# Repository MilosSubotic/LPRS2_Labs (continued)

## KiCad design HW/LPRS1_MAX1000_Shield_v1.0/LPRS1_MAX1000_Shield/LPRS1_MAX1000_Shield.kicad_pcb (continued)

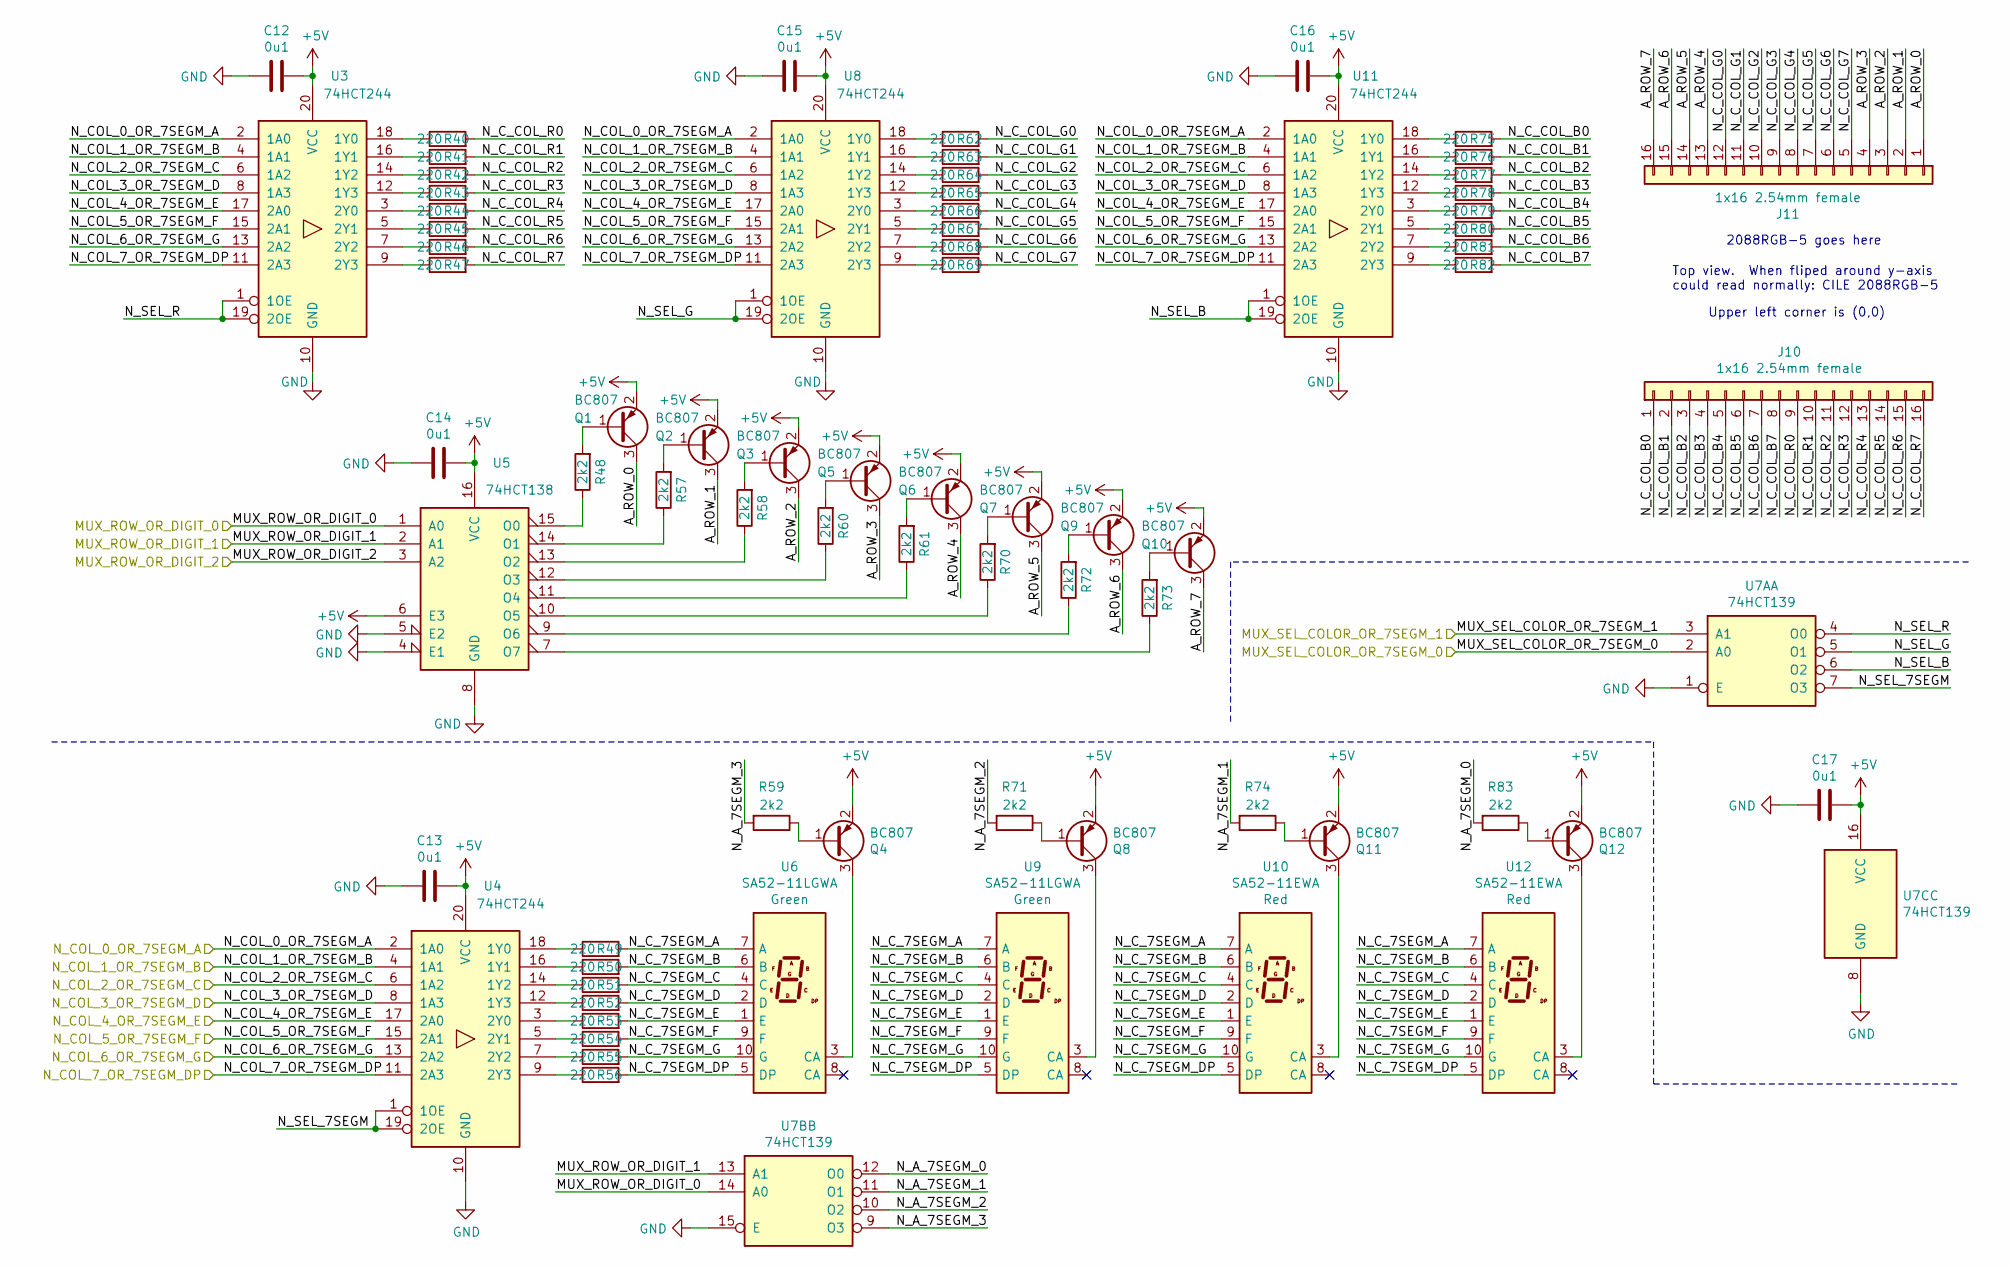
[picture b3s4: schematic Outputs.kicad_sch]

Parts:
C12, C13, C14, C15, C16, C17: 0u1; C_0805_2012Metric_Pad1.15x1.40mm_HandSolder
J10, J11: 1x16 2.54mm female; PinSocket_1x16_P2.54mm_Vertical
Q1, Q2, Q3, Q4, Q5, Q6, Q7, Q8, Q9, Q10, Q11, Q12: BC807; SOT-23
R40, R41, R42, R43, R44, R45, R46, R47, R49, R50, R51, R52, R53, R54, R55, R56, R62, R63, R64, R65, R66, R67, R68, R69, R75, R76, R77, R78, R79, R80, R81, R82: 220; R_0805_2012Metric_Pad1.15x1.40mm_HandSolder
R48, R57, R58, R59, R60, R61, R70, R71, R72, R73, R74, R83: 2k2; R_0805_2012Metric_Pad1.15x1.40mm_HandSolder
U3, U4, U8, U11: 74HCT244; SOIC-20W_7.5x12.8mm_P1.27mm
U5: 74HCT138; SOIC-16_3.9x9.9mm_P1.27mm
U6, U9: SA52-11LGWA; 7SegmentLED_LTS6760_LTS6780
U7A, U7B, U7C: 74HCT139; SOIC-16_3.9x9.9mm_P1.27mm
U10, U12: SA52-11EWA; 7SegmentLED_LTS6760_LTS6780

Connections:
+5V: C12.1, C13.1, C14.1, C15.1, C16.1, C17.1, Q1.2 (E), Q2.2 (E), Q3.2 (E), Q4.2 (E), Q5.2 (E), Q6.2 (E), Q7.2 (E), Q8.2 (E), Q9.2 (E), Q10.2 (E), Q11.2 (E), Q12.2 (E), U3.20 (VCC), U4.20 (VCC), U5.6 (E3), U5.16 (VCC), U7C.16 (VCC), U8.20 (VCC), U11.20 (VCC); also elsewhere on the board
/Outputs/A_ROW_0: J11.1, Q1.3 (C)
/Outputs/A_ROW_1: J11.2, Q2.3 (C)
/Outputs/A_ROW_2: J11.3, Q3.3 (C)
/Outputs/A_ROW_3: J11.4, Q5.3 (C)
/Outputs/A_ROW_4: J11.13, Q6.3 (C)
/Outputs/A_ROW_5: J11.14, Q7.3 (C)
/Outputs/A_ROW_6: J11.15, Q9.3 (C)
/Outputs/A_ROW_7: J11.16, Q10.3 (C)
/Outputs/MUX_ROW_OR_DIGIT_0: U5.1 (A0), U7B.14 (A0); also elsewhere on the board
/Outputs/MUX_ROW_OR_DIGIT_1: U5.2 (A1), U7B.13 (A1); also elsewhere on the board
/Outputs/MUX_ROW_OR_DIGIT_2: U5.3 (A2); also elsewhere on the board
/Outputs/N_A_7SEGM_0: R83.2, U7B.12 (O0); also elsewhere on the board
/Outputs/N_A_7SEGM_1: R74.2, U7B.11 (O1); also elsewhere on the board
/Outputs/N_A_7SEGM_2: R71.2, U7B.10 (O2); also elsewhere on the board
/Outputs/N_A_7SEGM_3: R59.2, U7B.9 (O3); also elsewhere on the board
/Outputs/N_COL_0_OR_7SEGM_A: U3.2 (1A0), U4.2 (1A0), U8.2 (1A0), U11.2 (1A0); also elsewhere on the board
/Outputs/N_COL_1_OR_7SEGM_B: U3.4 (1A1), U4.4 (1A1), U8.4 (1A1), U11.4 (1A1); also elsewhere on the board
/Outputs/N_COL_2_OR_7SEGM_C: U3.6 (1A2), U4.6 (1A2), U8.6 (1A2), U11.6 (1A2); also elsewhere on the board
/Outputs/N_COL_3_OR_7SEGM_D: U3.8 (1A3), U4.8 (1A3), U8.8 (1A3), U11.8 (1A3); also elsewhere on the board
/Outputs/N_COL_4_OR_7SEGM_E: U3.17 (2A0), U4.17 (2A0), U8.17 (2A0), U11.17 (2A0); also elsewhere on the board
/Outputs/N_COL_5_OR_7SEGM_F: U3.15 (2A1), U4.15 (2A1), U8.15 (2A1), U11.15 (2A1); also elsewhere on the board
/Outputs/N_COL_6_OR_7SEGM_G: U3.13 (2A2), U4.13 (2A2), U8.13 (2A2), U11.13 (2A2); also elsewhere on the board
/Outputs/N_COL_7_OR_7SEGM_DP: U3.11 (2A3), U4.11 (2A3), U8.11 (2A3), U11.11 (2A3); also elsewhere on the board
/Outputs/N_C_7SEGM_A: R49.2, U6.7 (A), U9.7 (A), U10.7 (A), U12.7 (A)
/Outputs/N_C_7SEGM_B: R50.2, U6.6 (B), U9.6 (B), U10.6 (B), U12.6 (B)
/Outputs/N_C_7SEGM_C: R51.2, U6.4 (C), U9.4 (C), U10.4 (C), U12.4 (C)
/Outputs/N_C_7SEGM_D: R52.2, U6.2 (D), U9.2 (D), U10.2 (D), U12.2 (D)
/Outputs/N_C_7SEGM_DP: R56.2, U6.5 (DP), U9.5 (DP), U10.5 (DP), U12.5 (DP)
/Outputs/N_C_7SEGM_E: R53.2, U6.1 (E), U9.1 (E), U10.1 (E), U12.1 (E)
/Outputs/N_C_7SEGM_F: R54.2, U6.9 (F), U9.9 (F), U10.9 (F), U12.9 (F)
/Outputs/N_C_7SEGM_G: R55.2, U6.10 (G), U9.10 (G), U10.10 (G), U12.10 (G)
/Outputs/N_C_COL_B0: J10.1, R75.2
/Outputs/N_C_COL_B1: J10.2, R76.2
/Outputs/N_C_COL_B2: J10.3, R77.2
/Outputs/N_C_COL_B3: J10.4, R78.2
/Outputs/N_C_COL_B4: J10.5, R79.2
/Outputs/N_C_COL_B5: J10.6, R80.2
/Outputs/N_C_COL_B6: J10.7, R81.2
/Outputs/N_C_COL_B7: J10.8, R82.2
/Outputs/N_C_COL_G0: J11.12, R62.2
/Outputs/N_C_COL_G1: J11.11, R63.2
/Outputs/N_C_COL_G2: J11.10, R64.2
/Outputs/N_C_COL_G3: J11.9, R65.2
/Outputs/N_C_COL_G4: J11.8, R66.2
/Outputs/N_C_COL_G5: J11.7, R67.2
/Outputs/N_C_COL_G6: J11.6, R68.2
/Outputs/N_C_COL_G7: J11.5, R69.2
/Outputs/N_C_COL_R0: J10.9, R40.2
/Outputs/N_C_COL_R1: J10.10, R41.2
/Outputs/N_C_COL_R2: J10.11, R42.2
/Outputs/N_C_COL_R3: J10.12, R43.2
/Outputs/N_C_COL_R4: J10.13, R44.2
/Outputs/N_C_COL_R5: J10.14, R45.2
/Outputs/N_C_COL_R6: J10.15, R46.2
/Outputs/N_C_COL_R7: J10.16, R47.2
/Outputs/N_SEL_7SEGM: U4.1 (1OE), U4.19 (2OE), U7A.7 (O3); also elsewhere on the board
/Outputs/N_SEL_B: U7A.6 (O2), U11.1 (1OE), U11.19 (2OE); also elsewhere on the board
/Outputs/N_SEL_G: U7A.5 (O1), U8.1 (1OE), U8.19 (2OE); also elsewhere on the board
/Outputs/N_SEL_R: U3.1 (1OE), U3.19 (2OE), U7A.4 (O0); also elsewhere on the board
GND: C12.2, C13.2, C14.2, C15.2, C16.2, C17.2, U3.10 (GND), U4.10 (GND), U5.4 (E1), U5.5 (E2), U5.8 (GND), U7A.1 (E), U7B.15 (E), U7C.8 (GND), U8.10 (GND), U11.10 (GND); also elsewhere on the board
unnamed: Q1.1 (B), R48.2
unnamed: Q2.1 (B), R57.2
unnamed: Q3.1 (B), R58.2
unnamed: Q4.1 (B), R59.1
unnamed: Q4.3 (C), U6.3 (CA)
unnamed: Q5.1 (B), R60.2
unnamed: Q6.1 (B), R61.2
unnamed: Q7.1 (B), R70.2
unnamed: Q8.1 (B), R71.1
unnamed: Q8.3 (C), U9.3 (CA)
unnamed: Q9.1 (B), R72.2
unnamed: Q10.1 (B), R73.2
unnamed: Q11.1 (B), R74.1
unnamed: Q11.3 (C), U10.3 (CA)
unnamed: Q12.1 (B), R83.1
unnamed: Q12.3 (C), U12.3 (CA)
unnamed: R40.1, U3.18 (1Y0)
unnamed: R41.1, U3.16 (1Y1)
unnamed: R42.1, U3.14 (1Y2)
unnamed: R43.1, U3.12 (1Y3)
unnamed: R44.1, U3.3 (2Y0)
unnamed: R45.1, U3.5 (2Y1)
unnamed: R46.1, U3.7 (2Y2)
unnamed: R47.1, U3.9 (2Y3)
unnamed: R48.1, U5.15 (O0)
unnamed: R49.1, U4.18 (1Y0)
unnamed: R50.1, U4.16 (1Y1)
unnamed: R51.1, U4.14 (1Y2)
unnamed: R52.1, U4.12 (1Y3)
unnamed: R53.1, U4.3 (2Y0)
unnamed: R54.1, U4.5 (2Y1)
unnamed: R55.1, U4.7 (2Y2)
unnamed: R56.1, U4.9 (2Y3)
unnamed: R57.1, U5.14 (O1)
unnamed: R58.1, U5.13 (O2)
unnamed: R60.1, U5.12 (O3)
unnamed: R61.1, U5.11 (O4)
unnamed: R62.1, U8.18 (1Y0)
unnamed: R63.1, U8.16 (1Y1)
unnamed: R64.1, U8.14 (1Y2)
unnamed: R65.1, U8.12 (1Y3)
unnamed: R66.1, U8.3 (2Y0)
unnamed: R67.1, U8.5 (2Y1)
unnamed: R68.1, U8.7 (2Y2)
unnamed: R69.1, U8.9 (2Y3)
unnamed: R70.1, U5.10 (O5)
unnamed: R72.1, U5.9 (O6)
unnamed: R73.1, U5.7 (O7)
unnamed: R75.1, U11.18 (1Y0)
unnamed: R76.1, U11.16 (1Y1)
unnamed: R77.1, U11.14 (1Y2)
unnamed: R78.1, U11.12 (1Y3)
unnamed: R79.1, U11.3 (2Y0)
unnamed: R80.1, U11.5 (2Y1)
unnamed: R81.1, U11.7 (2Y2)
unnamed: R82.1, U11.9 (2Y3)

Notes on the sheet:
2088RGB-5 goes here
Top view. When fliped around y-axis could read normally: CILE 2088RGB-5
Upper left corner is (0,0)

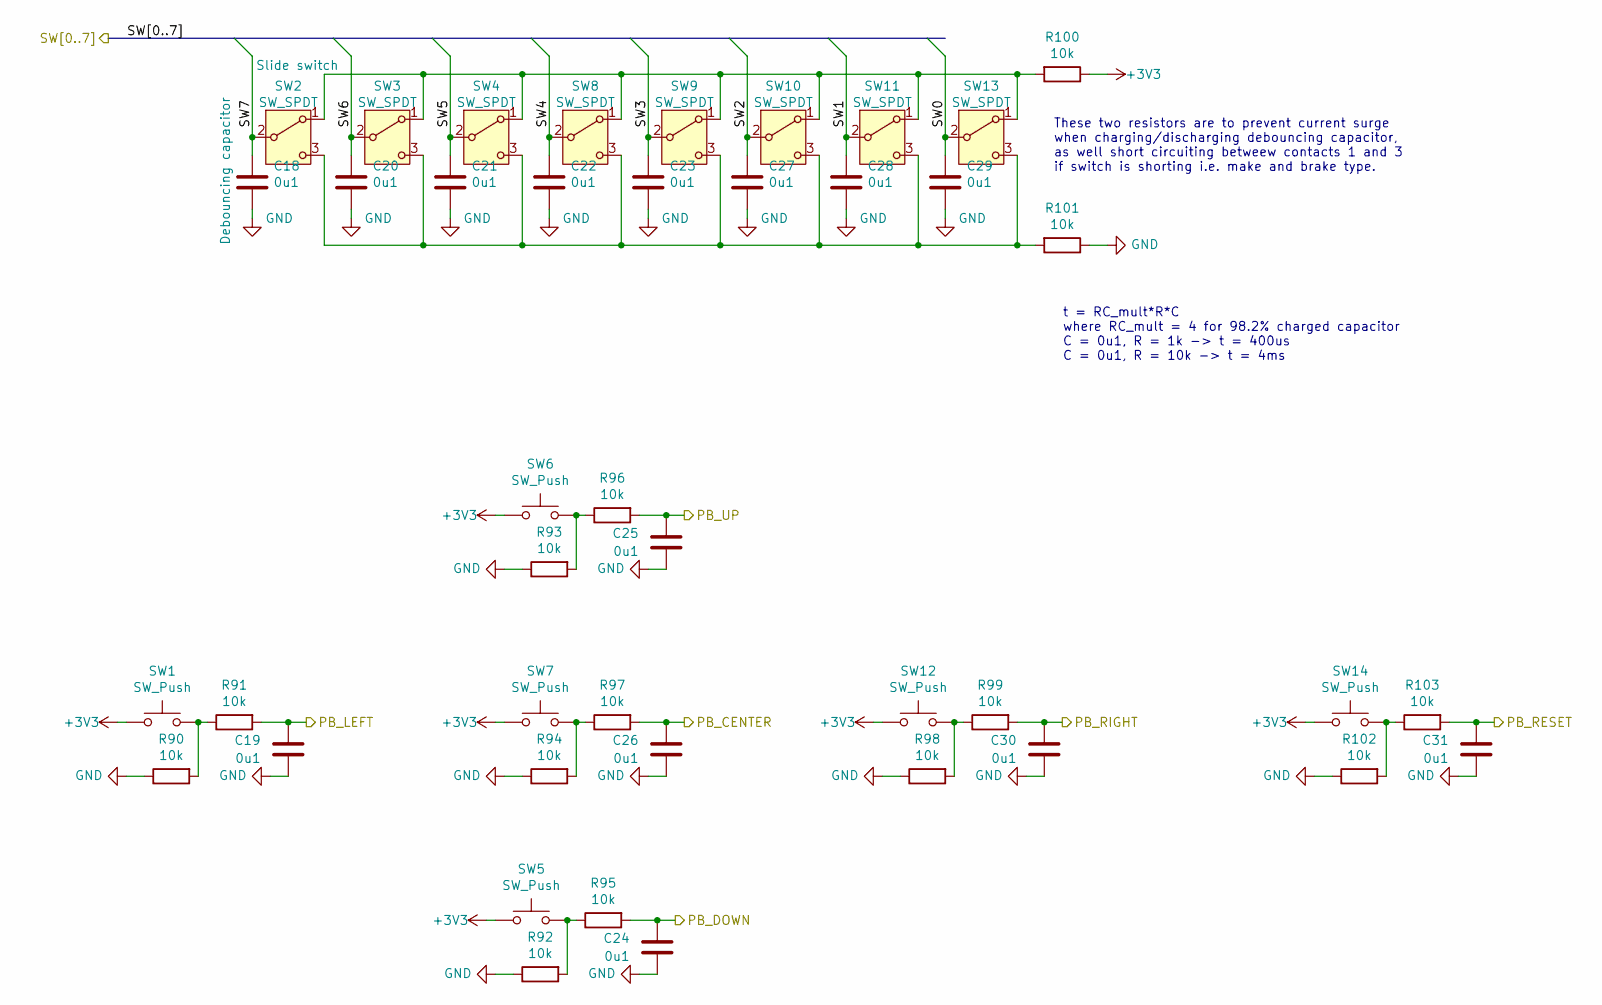
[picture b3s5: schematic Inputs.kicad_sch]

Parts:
C18, C19, C20, C21, C22, C23, C24, C25, C26, C27, C28, C29, C30, C31: 0u1; C_0805_2012Metric_Pad1.15x1.40mm_HandSolder
R90, R91, R92, R93, R94, R95, R96, R97, R98, R99, R100, R101, R102, R103: 10k; R_0805_2012Metric_Pad1.15x1.40mm_HandSolder
SW1, SW5, SW6, SW7, SW12, SW14: SW_Push; SW_PUSH_6mm_H7.3mm
SW2, SW3, SW4, SW8, SW9, SW10, SW11, SW13: SW_SPDT; OS102011MS2QN1

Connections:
+3V3: R100.1, SW1.2, SW5.2, SW6.2, SW7.2, SW12.2, SW14.2; also elsewhere on the board
/Inputs/PB_CENTER: C26.1, R97.2; also elsewhere on the board
/Inputs/PB_DOWN: C24.1, R95.2; also elsewhere on the board
/Inputs/PB_LEFT: C19.1, R91.2; also elsewhere on the board
/Inputs/PB_RESET: C31.1, R103.2; also elsewhere on the board
/Inputs/PB_RIGHT: C30.1, R99.2; also elsewhere on the board
/Inputs/PB_UP: C25.1, R96.2; also elsewhere on the board
/SW0: C29.1, SW13.2 (B); also elsewhere on the board
/SW1: C28.1, SW11.2 (B); also elsewhere on the board
/SW2: C27.1, SW10.2 (B); also elsewhere on the board
/SW3: C23.1, SW9.2 (B); also elsewhere on the board
/SW4: C22.1, SW8.2 (B); also elsewhere on the board
/SW5: C21.1, SW4.2 (B); also elsewhere on the board
/SW6: C20.1, SW3.2 (B); also elsewhere on the board
/SW7: C18.1, SW2.2 (B); also elsewhere on the board
GND: C18.2, C19.2, C20.2, C21.2, C22.2, C23.2, C24.2, C25.2, C26.2, C27.2, C28.2, C29.2, C30.2, C31.2, R90.1, R92.1, R93.1, R94.1, R98.1, R101.1, R102.1, SW2.shield, SW3.shield, SW4.shield, SW8.shield, SW9.shield, SW10.shield, SW11.shield, SW13.shield; also elsewhere on the board
unnamed: R90.2, R91.1, SW1.1
unnamed: R92.2, R95.1, SW5.1
unnamed: R93.2, R96.1, SW6.1
unnamed: R94.2, R97.1, SW7.1
unnamed: R98.2, R99.1, SW12.1
unnamed: R100.2, SW2.1 (A), SW3.1 (A), SW4.1 (A), SW8.1 (A), SW9.1 (A), SW10.1 (A), SW11.1 (A), SW13.1 (A)
unnamed: R101.2, SW2.3 (C), SW3.3 (C), SW4.3 (C), SW8.3 (C), SW9.3 (C), SW10.3 (C), SW11.3 (C), SW13.3 (C)
unnamed: R102.2, R103.1, SW14.1

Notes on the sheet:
t = RC_mult*R*C where RC_mult = 4 for 98.2% charged capacitor C = 0u1, R = 1k -> t = 400us C = 0u1, R = 10k -> t = 4ms
These two resistors are to prevent current surge when charging/discharging debouncing capacitor, as well short circuiting betweew contacts 1 and 3 if switch is shorting i.e. make and brake type.

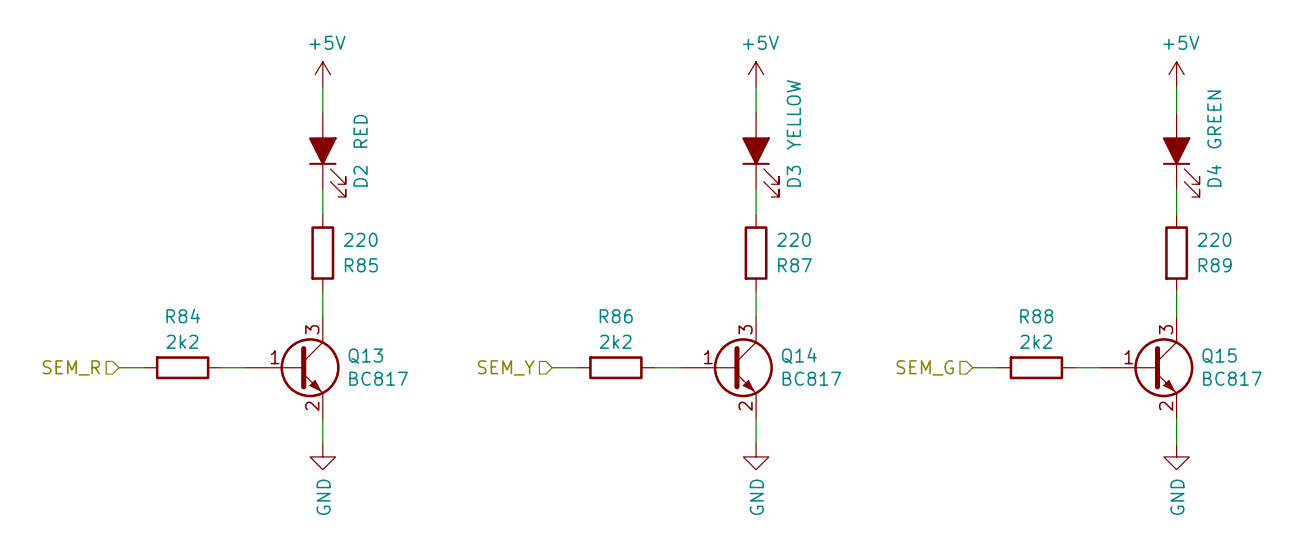
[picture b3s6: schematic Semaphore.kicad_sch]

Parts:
D2: RED; LED_D5.0mm_Clear
D3: YELLOW; LED_D5.0mm_Clear
D4: GREEN; LED_D5.0mm_Clear
Q13, Q14, Q15: BC817; SOT-23
R84, R86, R88: 2k2; R_0805_2012Metric_Pad1.15x1.40mm_HandSolder
R85, R87, R89: 220; R_0805_2012Metric_Pad1.15x1.40mm_HandSolder

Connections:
+5V: D2.2 (A), D3.2 (A), D4.2 (A); also elsewhere on the board
/AIN6: R86.2; also elsewhere on the board
/AIN7: R88.2; also elsewhere on the board
/D13: R84.2; also elsewhere on the board
GND: Q13.2 (E), Q14.2 (E), Q15.2 (E); also elsewhere on the board
unnamed: D2.1 (K), R85.1
unnamed: D3.1 (K), R87.1
unnamed: D4.1 (K), R89.1
unnamed: Q13.1 (B), R84.1
unnamed: Q13.3 (C), R85.2
unnamed: Q14.1 (B), R86.1
unnamed: Q14.3 (C), R87.2
unnamed: Q15.1 (B), R88.1
unnamed: Q15.3 (C), R89.2

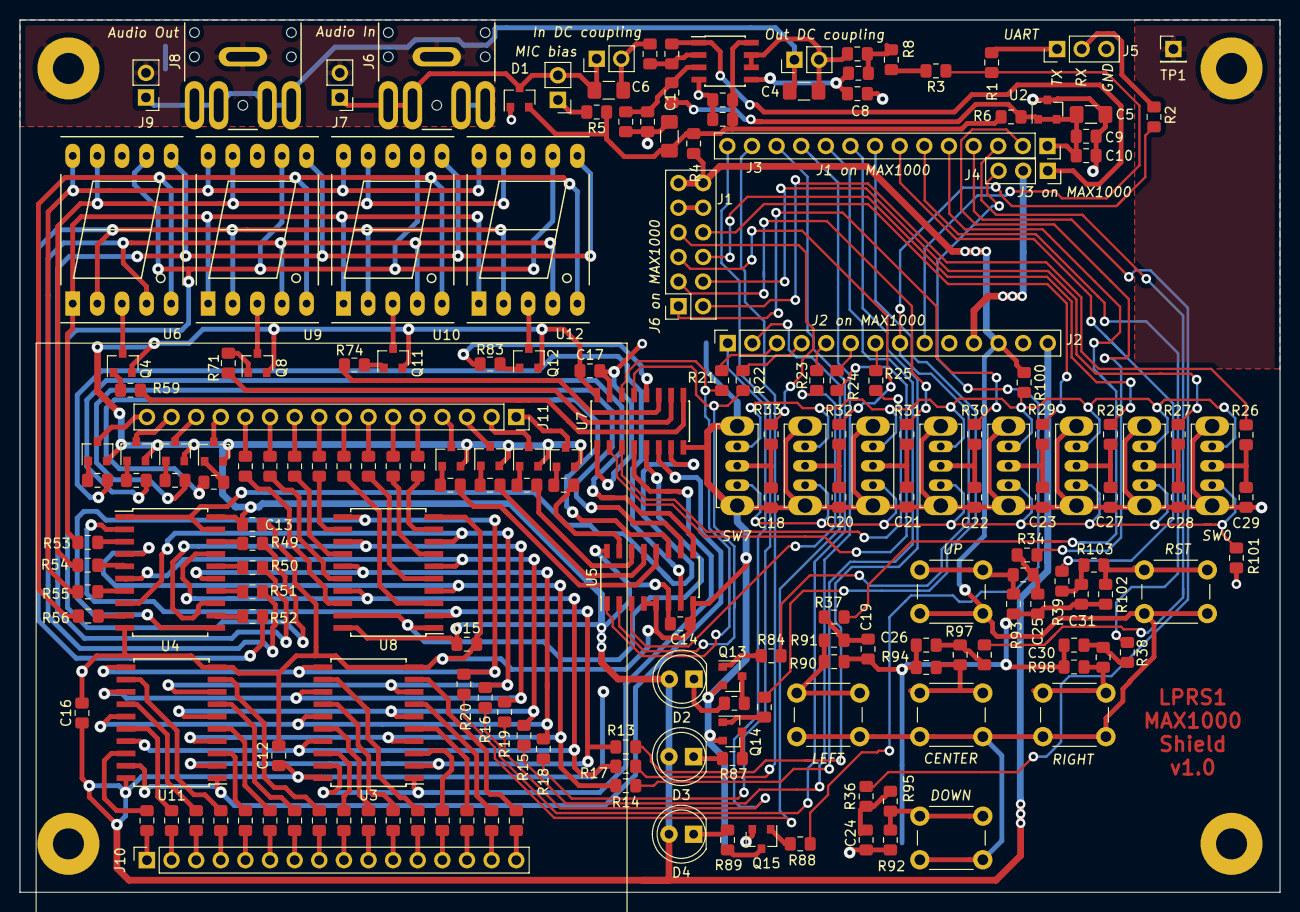
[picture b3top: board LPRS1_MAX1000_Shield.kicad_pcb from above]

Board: 2 copper layers, 130.0 x 90.0 mm, 198 parts (0 on the bottom side), 198 nets.

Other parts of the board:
U7: 74HCT139; SOIC-16_3.9x9.9mm_P1.27mm

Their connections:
+5V: U7.16; also elsewhere on the board
/Outputs/MUX_ROW_OR_DIGIT_0: U7.14; also elsewhere on the board
/Outputs/MUX_ROW_OR_DIGIT_1: U7.13; also elsewhere on the board
/Outputs/MUX_SEL_COLOR_OR_7SEGM_0: U7.2; also elsewhere on the board
/Outputs/MUX_SEL_COLOR_OR_7SEGM_1: U7.3; also elsewhere on the board
/Outputs/N_A_7SEGM_0: U7.12; also elsewhere on the board
/Outputs/N_A_7SEGM_1: U7.11; also elsewhere on the board
/Outputs/N_A_7SEGM_2: U7.10; also elsewhere on the board
/Outputs/N_A_7SEGM_3: U7.9; also elsewhere on the board
/Outputs/N_SEL_7SEGM: U7.7; also elsewhere on the board
/Outputs/N_SEL_B: U7.6; also elsewhere on the board
/Outputs/N_SEL_G: U7.5; also elsewhere on the board
/Outputs/N_SEL_R: U7.4; also elsewhere on the board
GND: U7.1, U7.8, U7.15; also elsewhere on the board

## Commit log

2026-03-14 Basic things.
2026-03-14 Move to correct places.
2026-03-14 Needed in future.
2026-03-14 Not needed.
2026-03-14 Update to new KiCAD version.
2026-03-14 Started new PCB.
2026-03-14 Newer git ignore.
2026-03-15 For start.
2026-03-15 Done shield.
2026-03-15 Optimizing.
2026-03-15 This is correct way.
2026-03-15 Better.
2026-03-15 Done.
2026-03-15 Started FW.
2026-03-15 Test working.
2026-03-16 New way.
2026-03-16 Another swap.
2026-03-17 Faster read.
2026-03-17 v0.3
2026-03-18 Lab.
2026-03-20 Spec.
2026-03-23 Adding HW.
2026-03-23 Ideas.
2026-03-23 New prj started.
2026-03-24 Done something.
2026-03-27 Done PCB.
2026-03-27 Small corrections.
2026-03-27 Correcting PCB
2026-03-27 PCB corrected.
2026-03-27 Resistors.
2026-03-28 Correction.
2026-03-28 Enc from robot.
2026-03-28 Connector orientations correction.
2026-03-29 Swapped GND and 5V so I can use internal Pull-up.
2026-03-29 Pins spreadsheet.
2026-03-31 Reordering.
2026-03-31 Better img.
2026-03-31 Bringup started.
2026-03-31 rotating stepper works fine
2026-03-31 Debugging LEDs
2026-03-31 Rotating LED
2026-03-31 All done.
2026-03-31 Corrections.
2026-03-31 ULN stuff working.
2026-04-02 FW example.
2026-04-02 Use Python3.
2026-04-02 PC side SW.
